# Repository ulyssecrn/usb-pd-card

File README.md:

# usb-pd-card

A credit-card-sized PCB business card that is also a **USB-C PD charger tester** and a **battery-free NFC tag**.

## What it does
- **USB-C PD tester:** plug any USB-C charger or cable into the card edge.
  - The CH32X035 MCU reads the charger's advertised capabilities and lights one LED each for 5 V / 9 V / 12 V / 15 V / 20 V / PPS / EPR.
  - A 5-LED bar shows max power: 15, 30, 45, 65, 100 W.
  - It only ever asks the charger for 5 V.
  - A charger without PD blinks the 5V LED (and lights 15W if it advertises 3 A on CC).
- **NFC:** tap a phone on the coil and it opens [ulysse.corne.sh](https://ulysse.corne.sh). No battery: the NT3H2111 tag and its LED run on energy harvested from the phone's field.

## Hardware
| | |
|---|---|
| Board | 85.6 × 54 mm (ID-1), 0.6 mm FR4, 2 layers, ENIG, matte black mask |
| USB-C | PCB-edge paddle, tongue cut into the board; CC1/CC2 with 5.1 kΩ Rd + ESD |
| MCU | WCH CH32X035G8U6 (RISC-V, built-in USB PD PHY) |
| Power | ME6228 3.3 V LDO from VBUS, SMF20A TVS |
| NFC | NXP NT3H2111 + on-board 5-turn coil (≈ 2.3 µH estimated) |
| Assembly | JLCPCB PCBA, all parts on the front |

## Repo layout
- `usb-pd-card.kicad_*`: KiCad 10 project (schematic + PCB)
- `lib/`: project symbols and footprints (USB-C paddle derived from [flip-card](https://github.com/Nicholas-L-Johnson/flip-card), MIT)
- `lib/nfc-coils.pretty/`: generated NFC coil footprints
- `tools/nfc_coil.py`: coil generator and inductance estimator (plain Python, no dependencies). Try `python3 tools/nfc_coil.py selftest`.
- `firmware/`: CH32X035 firmware (ch32fun, `nix-shell`, flashed with an RP2040 programmer). See [`firmware/README.md`](firmware/README.md).
- `jlcpcb/`: v1 production files (Gerbers, BOM, CPL)
- `AGENTS.md`: full design notes, pin map and decisions

## Status
- **v1 works.** 30 boards built by JLCPCB, received in October 2026.
- **USB-C PD:** the firmware reads every charger tried correctly, in both plug orientations (Apple, Anker, Lenovo, GaN chargers, power banks, plain 5 V chargers).
- **NFC:** a phone tap opens the site, and the NFC LED lights from the phone's field. The NT3H2111 ships unformatted and must be formatted once per card (see `AGENTS.md`).
- **Still to do:** measure the coil's resonance and choose the tuning capacitor (C3), test NFC read range, and flash and program the remaining cards.

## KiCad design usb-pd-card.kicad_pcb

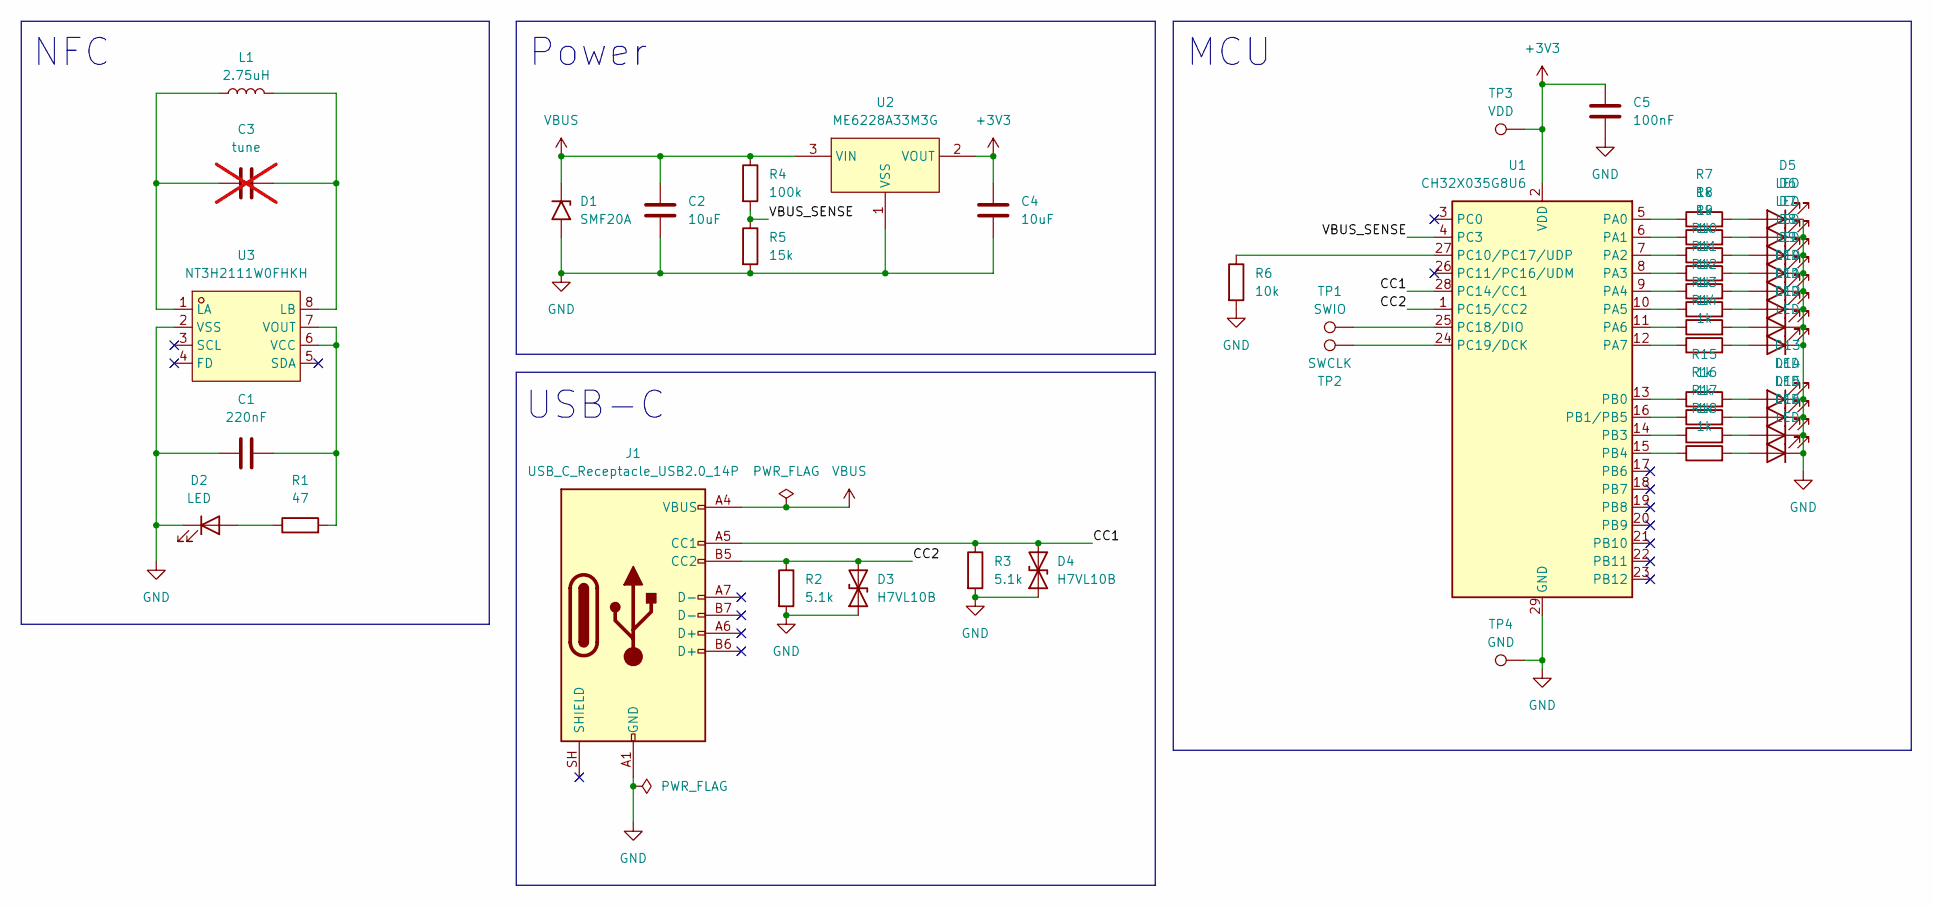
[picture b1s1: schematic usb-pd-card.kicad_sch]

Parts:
C1: 220nF; C_0402_1005Metric; LCSC C16772
C2: 10uF; C_0603_1608Metric; LCSC C96446
C3: tune; C_0402_1005Metric; not fitted
C4: 10uF; C_0603_1608Metric; LCSC C19702
C5: 100nF; C_0402_1005Metric; LCSC C1525
D1: SMF20A; D_SOD-123F; LCSC C41411782
D2, D5, D6, D7, D8, D9, D10, D11, D12, D13, D14, D15, D16: LED; LED_0603_1608Metric; LCSC C2286
D3, D4: H7VL10B; D_0402_1005Metric; LCSC C20615787
J1: USB_C_Receptacle_USB2.0_14P; USB_C_Paddle
L1: 2.75uH; NFC_Coil_Rect_38x46mm_R4_5T_W0.5_S0.3
R1: 47; R_0402_1005Metric; LCSC C25118
R2, R3: 5.1k; R_0402_1005Metric; LCSC C25905
R4: 100k; R_0402_1005Metric; LCSC C25741
R5: 15k; R_0402_1005Metric; LCSC C25756
R6: 10k; R_0402_1005Metric; LCSC C25744
R7, R8, R9, R10, R11, R12, R13, R14, R15, R16, R17, R18: 1k; R_0402_1005Metric; LCSC C11702
TP1: SWIO; TestPoint_Pad_1.0x1.0mm
TP2: SWCLK; TestPoint_Pad_1.0x1.0mm
TP3: VDD; TestPoint_Pad_1.0x1.0mm
TP4: GND; TestPoint_Pad_1.0x1.0mm
U1: CH32X035G8U6; WQFN-28-1EP_4x4mm_P0.4mm_EP2.7x2.7mm; LCSC C7437027
U2: ME6228A33M3G; SOT-23-3_L2.9-W1.6-P1.90-LS2.8-BR; MPN ME6228A33M3G; LCSC C487914
U3: NT3H2111W0FHKH; XQFN-8_L1.6-W1.6-P0.50-BL_NT3H2111W0FHKH; MPN NT3H2111W0FHKH; LCSC C710403

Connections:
+3V3: C4.1, C5.1, TP3.1 (1_1), U1.2 (VDD), U2.2 (VOUT)
/CC1: D4.2 (A2), J1.A5 (CC1), R3.1, U1.28 (PC14/CC1)
/CC2: D3.2 (A2), J1.B5 (CC2), R2.1, U1.1 (PC15/CC2)
/VBUS_SENSE: R4.2, R5.1, U1.4 (PC3)
GND: C1.1, C2.2, C4.2, C5.2, D1.2 (A2), D2.1 (K), D3.1 (A1), D4.1 (A1), D5.1 (K), D6.1 (K), D7.1 (K), D8.1 (K), D9.1 (K), D10.1 (K), D11.1 (K), D12.1 (K), D13.1 (K), D14.1 (K), D15.1 (K), D16.1 (K), J1.A1 (GND), J1.A12 (GND), J1.B1 (GND), J1.B12 (GND), R2.2, R3.2, R5.2, R6.2, TP4.1 (1_1), U1.29 (GND), U2.1 (VSS), U3.2 (VSS)
unnamed: D2.2 (A), R1.1
unnamed: D5.2 (A), R7.2
unnamed: D6.2 (A), R8.2
unnamed: D7.2 (A), R9.2
unnamed: D8.2 (A), R10.2
unnamed: D9.2 (A), R11.2
unnamed: D10.2 (A), R12.2
unnamed: D11.2 (A), R13.2
unnamed: D12.2 (A), R14.2
unnamed: D13.2 (A), R15.2
unnamed: D14.2 (A), R16.2
unnamed: D15.2 (A), R17.2
unnamed: D16.2 (A), R18.2
unnamed: R7.1, U1.5 (PA0)
unnamed: R8.1, U1.6 (PA1)
unnamed: R9.1, U1.7 (PA2)
unnamed: R10.1, U1.8 (PA3)
unnamed: R11.1, U1.9 (PA4)
unnamed: R12.1, U1.10 (PA5)
unnamed: R13.1, U1.11 (PA6)
unnamed: R14.1, U1.12 (PA7)
unnamed: R15.1, U1.13 (PB0)
unnamed: R16.1, U1.16 (PB1/PB5)
unnamed: R17.1, U1.14 (PB3)
unnamed: R18.1, U1.15 (PB4)
unnamed: R6.1, U1.27 (PC10/PC17/UDP)
unnamed: TP1.1 (1_1), U1.25 (PC18/DIO)
unnamed: TP2.1 (1_1), U1.24 (PC19/DCK)
unnamed: C3.1, L1.1, U3.1 (LA)
unnamed: C3.2, L1.2, U3.8 (LB)
unnamed: C1.2, R1.2, U3.6 (VCC), U3.7 (VOUT)
VBUS: C2.1, D1.1 (A1), J1.A4 (VBUS), J1.A9 (VBUS), J1.B4 (VBUS), J1.B9 (VBUS), R4.1, U2.3 (VIN)

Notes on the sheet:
MCU
USB-C
Power
NFC

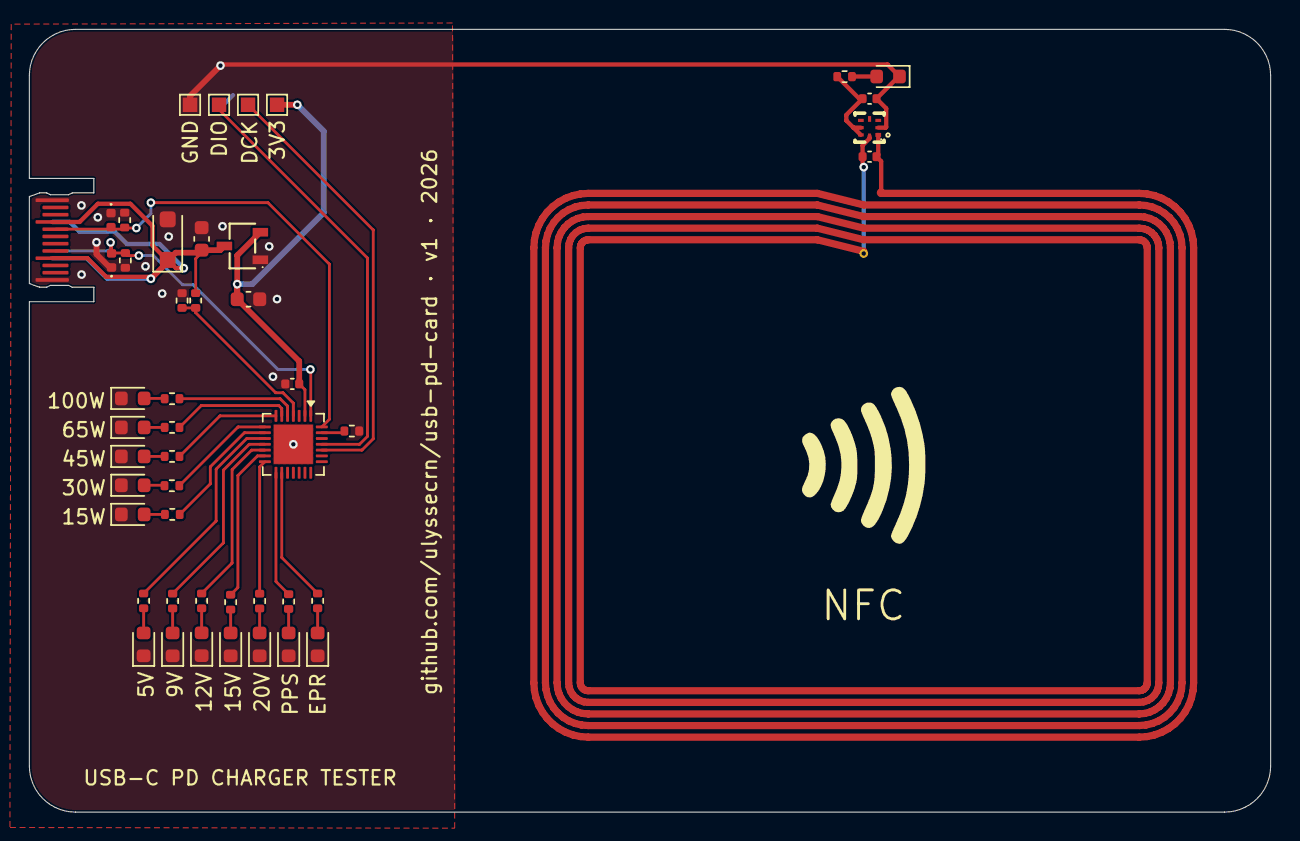
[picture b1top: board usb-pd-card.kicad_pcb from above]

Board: 2 copper layers, 85.6 x 54.0 mm, 48 parts (0 on the bottom side), 37 nets.

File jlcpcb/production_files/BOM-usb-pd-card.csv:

Comment,Designator,Footprint,LCSC,Quantity
100k,R4,R_0402_1005Metric,C25741,1
100nF,C5,C_0402_1005Metric,C1525,1
10k,R6,R_0402_1005Metric,C25744,1
10uF,C4,C_0603_1608Metric,C19702,1
10uF,C2,C_0603_1608Metric,C96446,1
15k,R5,R_0402_1005Metric,C25756,1
1k,"R10,R11,R12,R13,R14,R15,R16,R17,R18,R7,R8,R9",R_0402_1005Metric,C11702,12
220nF,C1,C_0402_1005Metric,C16772,1
47,R1,R_0402_1005Metric,C25118,1
5.1k,"R2,R3",R_0402_1005Metric,C25905,2
CH32X035G8U6,U1,WQFN-28-1EP_4x4mm_P0.4mm_EP2.7x2.7mm,C7437027,1
H7VL10B,"D3,D4",D_0402_1005Metric,C20615787,2
LED,"D10,D11,D12,D13,D14,D15,D16,D2,D5,D6,D7,D8,D9",LED_0603_1608Metric,C2286,13
ME6228A33M3G,U2,SOT-23-3_L2.9-W1.6-P1.90-LS2.8-BR,C487914,1
NT3H2111W0FHKH,U3,XQFN-8_L1.6-W1.6-P0.50-BL_NT3H2111W0FHKH,C710403,1
SMF20A,D1,D_SOD-123F,C41411782,1

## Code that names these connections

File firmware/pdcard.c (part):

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#define BIT( led ) ( 1u << ( led ) )

static const uint8_t s_ledPins[LED_COUNT] = {
	[LED_5V] = PA5,
	[LED_9V] = PA6,
	[LED_12V] = PA7,
	[LED_15V] = PB0,
	[LED_20V] = PB3,
	[LED_PPS] = PB4,
	[LED_EPR] = PB1, // PB1 shares pin 16 with PB5: never configure PB5
	[LED_15W] = PA4,
	[LED_30W] = PA3,
	[LED_45W] = PA2,
	[LED_65W] = PA1,
	[LED_100W] = PA0,
};

static const struct
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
